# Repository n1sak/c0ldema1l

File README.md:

# c0ld ema1l // tldr - a keypad to help you with your job search!

Hi! This is **c0ld ema1l**, my custom 6-button keypad designed to make applying for jobs easier! 
This project was inspired by my experience cold emailing for opportunities, a process now streamlined with this automated keypad

---
# Photos

---

## Features

- 6 mechanical keys, each one types out a different piece of a job application:
  - Cold email intro
  - Portfolio link
  - Closing line
  - Resume link
  - Thank you follow-up
  - Last key types Soham Parekh’s full cold email template :D 
- Combo keys -- you press 2 at once to:
  - Open LinkedIn
  - Open GitHub
  - Open Google Sheets

---

## PCB

I designed the PCB in KiCad. There are 6 switches in a simple matrix and a USB-C connector. DRC passed with zero errors.

---

## CAD Model

The 3D printed case holds everything and has space for the USB port and switches.

---

## Firmware

The firmware is a file included in my Firmware folder as main.py. This project uses KMK firmware.
- Types text over USB.
- Custom combos detect when 2 keys are pressed to launch websites automatically.

---

## Bill of Materials (BOM)

6x MX-Style Switches

6x DSA Blank White Keycaps

2x SK6812 MINI-E RGB LEDs

1x Seeed XIAO RP2040 (microcontroller :) )

1x Case (2 printed parts)

4x M3 × 16 mm pan-head screws

1x USB-C Cable

---

## How it works

1. Plug it into your computer via USB-C.
2. Press any key: parts of a cold email are typed out for you instantly.
3. Press combos: directed to LinkedIn, GitHub, or Google Sheets.
---

Made + Submitted to Hacklub's Highway hackathon.

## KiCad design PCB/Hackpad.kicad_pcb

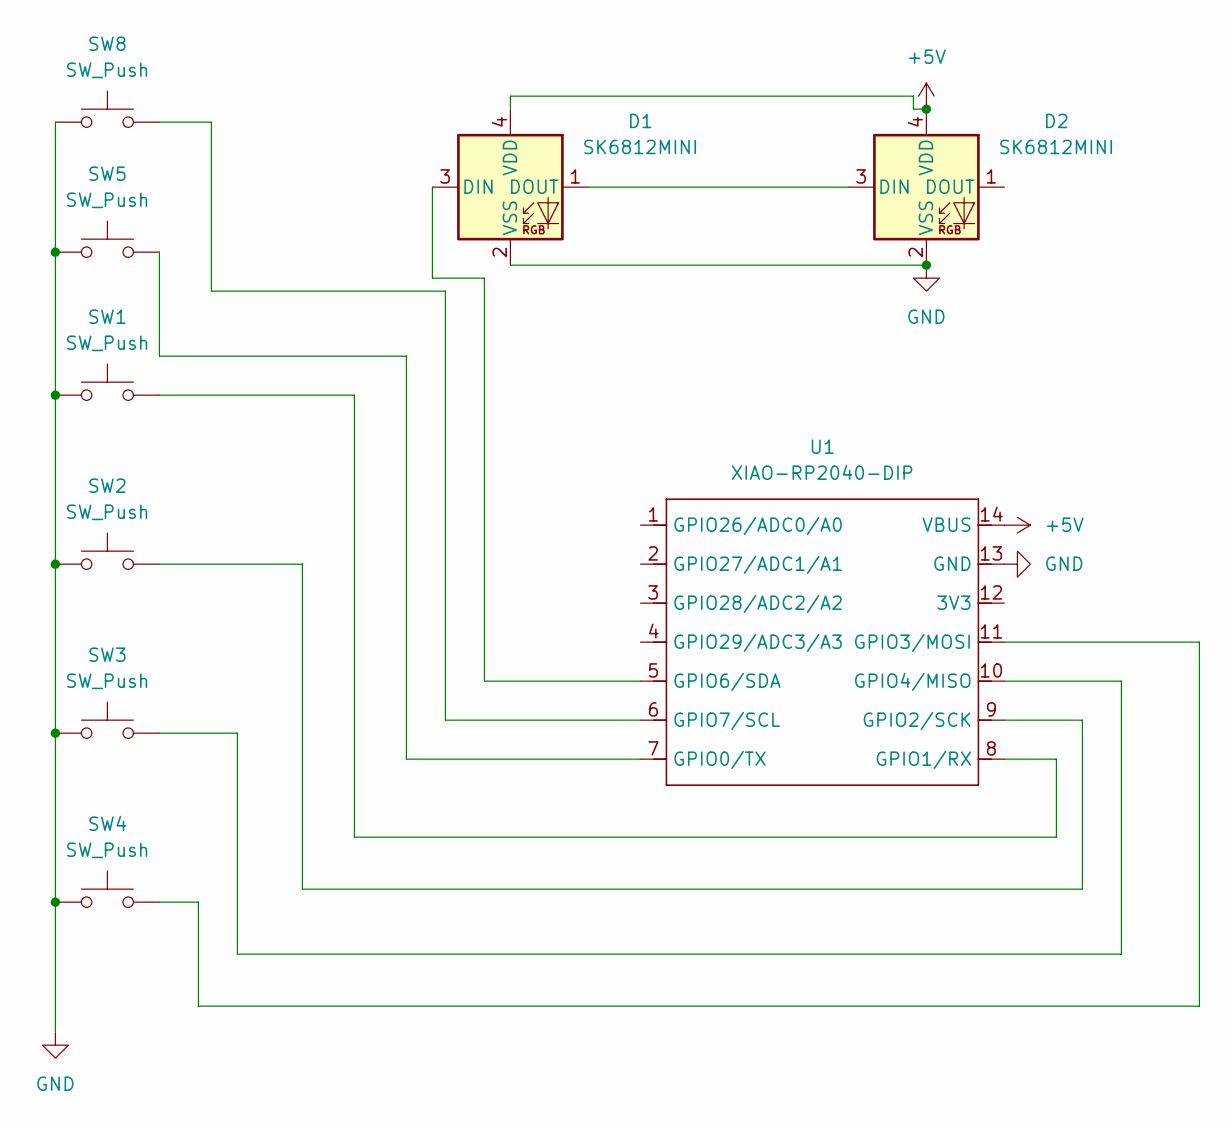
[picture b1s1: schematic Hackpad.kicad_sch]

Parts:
D1, D2: SK6812MINI; LED_SK6812MINI_PLCC4_3.5x3.5mm_P1.75mm
SW1: SW_Push; SW_Cherry_MX_2.75u_PCB
SW2, SW3, SW4, SW5, SW8: SW_Push; SW_Cherry_MX_1.00u_PCB
U1: XIAO-RP2040-DIP

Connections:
+5V: D1.4 (VDD), D2.4 (VDD), U1.14 (VBUS)
GND: D1.2 (VSS), D2.2 (VSS), SW1.1, SW2.1, SW3.1, SW4.1, SW5.1, SW8.1, U1.13 (GND)
unnamed: D1.3 (DIN), U1.5 (GPIO6/SDA)
unnamed: D1.1 (DOUT), D2.3 (DIN)
unnamed: SW5.2, U1.7 (GPIO0/TX)
unnamed: SW1.2, U1.8 (GPIO1/RX)
unnamed: SW2.2, U1.9 (GPIO2/SCK)
unnamed: SW4.2, U1.11 (GPIO3/MOSI)
unnamed: SW3.2, U1.10 (GPIO4/MISO)
unnamed: SW8.2, U1.6 (GPIO7/SCL)

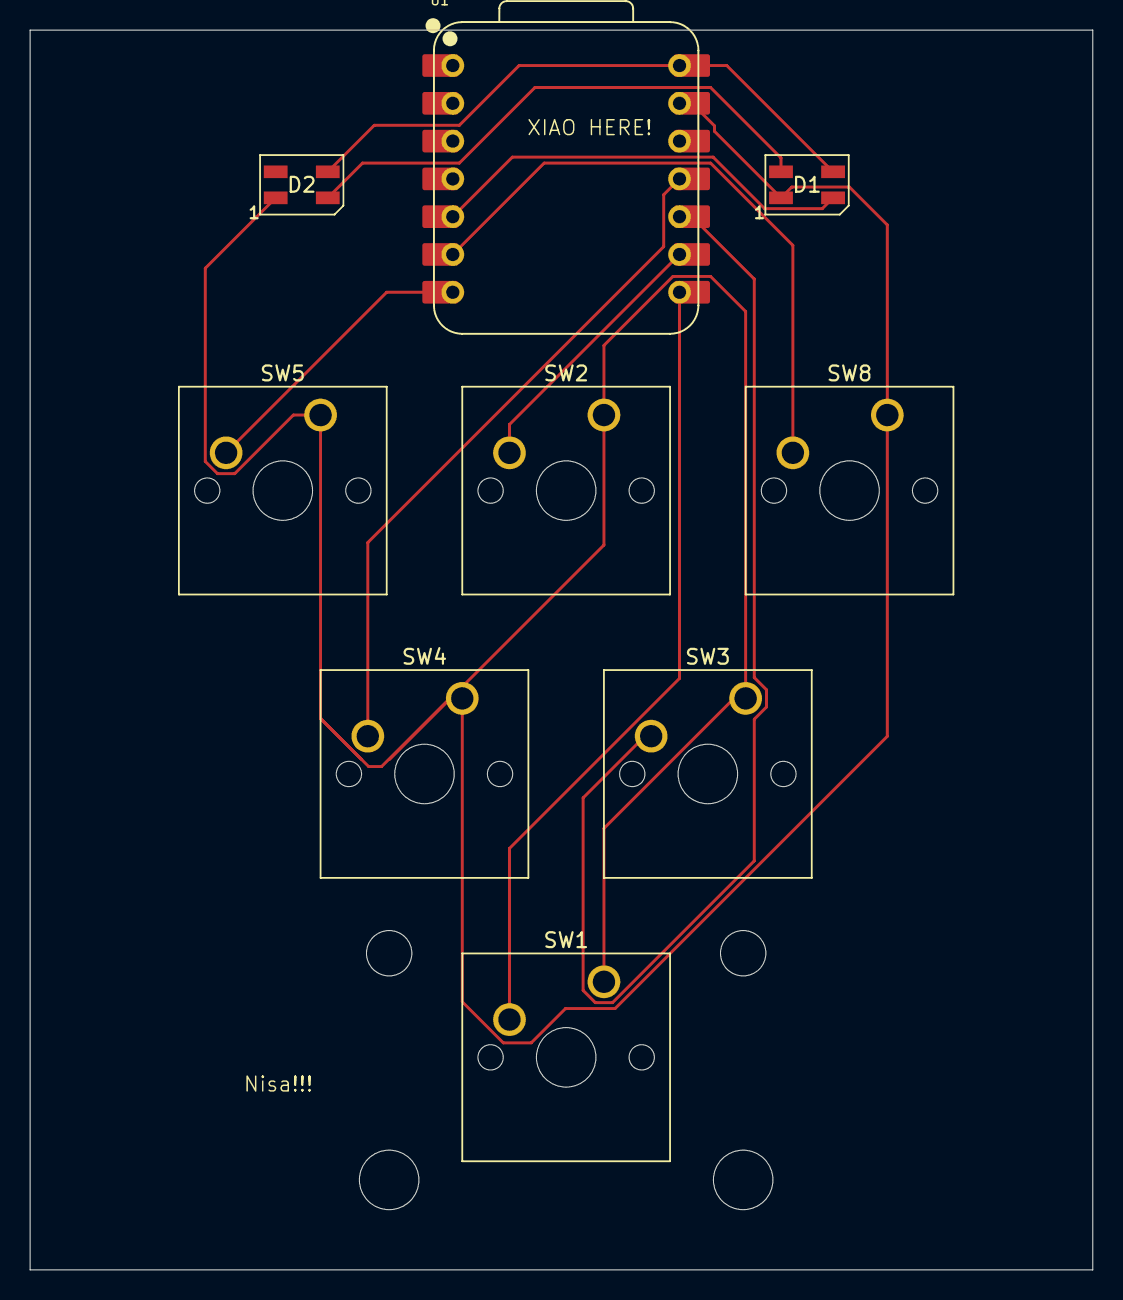
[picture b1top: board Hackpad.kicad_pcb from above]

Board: 2 copper layers, 71.4 x 83.3 mm, 9 parts (0 on the bottom side), 10 nets.

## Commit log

2025-07-02 hello
2025-07-07 Rename Firmware.py to main.py
